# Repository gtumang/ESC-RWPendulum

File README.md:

# ESC-RWPendulum

Este repositório contém o firmware, modelos de simulação e ferramentas de visualização para um sistema de controle de **Pêndulo com Roda de Reação** (Pêndulo Invertido). O projeto foi projetado para estabilizar o pêndulo usando uma roda de reação acionada por um motor DC, controlado por um microcontrolador ESP32.

## Estrutura do Projeto

O repositório está organizado em quatro diretórios principais:

* **`Firmware/`**: Código C++ embarcado para o ESP32, construído usando PlatformIO. Gerencia a leitura de sensores, a execução da malha de controle e a comunicação serial.
* **`Matlab/`**: Scripts MATLAB e modelos Simulink para definição de parâmetros físicos, modelagem matemática e cálculo de ganho de controle (LQR).
* **`Visualization/`**: Scripts Python para telemetria em tempo real, registro de dados e plotagem via Serial.
* **`PCB/`**: Arquivos de projeto da placa de circuito impresso (Hardware), incluindo esquemáticos, layout e arquivos de fabricação.

---

## 1. Firmware (ESP32)

O firmware está localizado no diretório `Firmware` e está configurado como um projeto **PlatformIO**.

### Configuração de Hardware
* **Microcontrolador**: ESP32 (Placa: `fm-devkit`)
* **Atuador**: Motor DC com driver PWM (controlado pelos pinos 25/26).
* **Sensores**: Dois Encoders de Quadratura (Ângulo do Pêndulo e Velocidade da Roda).

**Pinagem (`main.cpp`):**
| Componente | Pino A | Pino B | Notas |
| :--- | :--- | :--- | :--- |
| **Encoder da Roda** | GPIO 17 | GPIO 16 | Mede velocidade/posição da roda de reação |
| **Encoder do Pêndulo** | GPIO 19 | GPIO 18 | Mede o ângulo de inclinação do pêndulo |
| **Driver do Motor** | GPIO 25 | GPIO 26 | Saída PWM (LEDC) |
| **Botão Iniciar/Parar**| GPIO 4 | - | Alterna a malha de controle (ISR) |

### Malha de Controle
* **Algoritmo**: Controle em Espaço de Estados (LQR).
* **Frequência**: 50 Hz (`Ts = 0.02s`).
* **Estados**:
    1.  $x_1$: Ângulo do Pêndulo (rad)
    2.  $x_2$: Ângulo da Roda (rad)
    3.  $x_3$: Velocidade do Pêndulo (rad/s)
    4.  $x_4$: Velocidade da Roda (rad/s)
* **Comunicação**: Envia dados de estado e esforço de controle via Serial (Formato binário).

---
## 2. MATLAB & Simulação

O diretório `Matlab` contém a fundação matemática do projeto.

* **`Scripts/SalvaParams.m`**: Define as constantes físicas do sistema (massas, comprimentos, inércia, constantes do motor) e as salva em `Parametros/parametros_planta.mat`.
    * *Parâmetros incluem:* $M_h$ (Massa da haste), $M_r$ (Massa do rotor), $L$ (Comprimento), $J_h$ (Inércia), etc.
* **`PenduloRotativoSim.slx`**: Modelo Simulink para simular a dinâmica do sistema e a resposta do controlador.
* **`Funcoes/`**: Contém funções geradas automaticamente (`function_G_Rot`, `function_M_Rot`, etc.) para a simulação não linear do sistema.
* **`Parametros/`**: Armazena arquivos `.mat` com a matriz de ganho de controle `K` calculada.

**Como usar:**
1.  Edite os parâmetros físicos em `SalvaParams.m` e execute-o.
2.  Execute o script de análise principal (ex: `main.mlx`) para calcular a matriz de ganho LQR $K$.
3.  Atualize a struct `K` em `Firmware/src/main.cpp` com os valores calculados.

---

## 3. Visualização (Python)

O diretório `Visualization` fornece ferramentas para visualizar dados do sistema em tempo real.

### Requisitos
* Python 3.x
* Bibliotecas: `pyserial`, `matplotlib`

### Scripts
* **`ler_pendulo.py`**: Um utilitário simples para ler dados brutos da porta serial e imprimir os valores decodificados em ponto flutuante no console.
* **`plot_pendulo.py`**: Uma ferramenta de plotagem em tempo real.
    * **Uso**: `python plot_pendulo.py --port COM3`
    * **Recursos**:
        * Plota múltiplas variáveis dinamicamente.
        * Suporta um modo de simulação para testar a interface sem hardware: `python plot_pendulo.py --sim`.
        * Visualiza Ângulo, Velocidade e Esforço de Controle ($u$).

---

## 4. Hardware e PCB (KiCad)

O diretório **`PCB`** contém todo o projeto eletrônico necessário para fabricar a placa de controle customizada do pêndulo, desenvolvido no software **KiCad**.

### Estrutura dos Arquivos
* **`RWPendulum/`**: Contém os arquivos fonte do projeto KiCad, incluindo o esquemático (`.kicad_sch`) e o layout da PCB (`.kicad_pcb`). O design integra o módulo ESP32 DevKit V1 e o driver de motor.
* **`OutputFiles/`**: Arquivos gerados para fabricação da placa:
    * **`Gerber/`**: Arquivos Gerber para as camadas de cobre, máscara de solda e corte.
    * **`Drill/`**: Arquivos de furação (PTH e NPTH).
* **`3D/`**: Modelos 3D (.step) da placa completa e componentes específicos (ex: Driver MD36A) para visualização mecânica e validação de encaixe.

---

## Licença
*Nenhuma licença especificada nos arquivos do repositório*.

## Autor
**Gabriel Brunoro Motta Tumang**

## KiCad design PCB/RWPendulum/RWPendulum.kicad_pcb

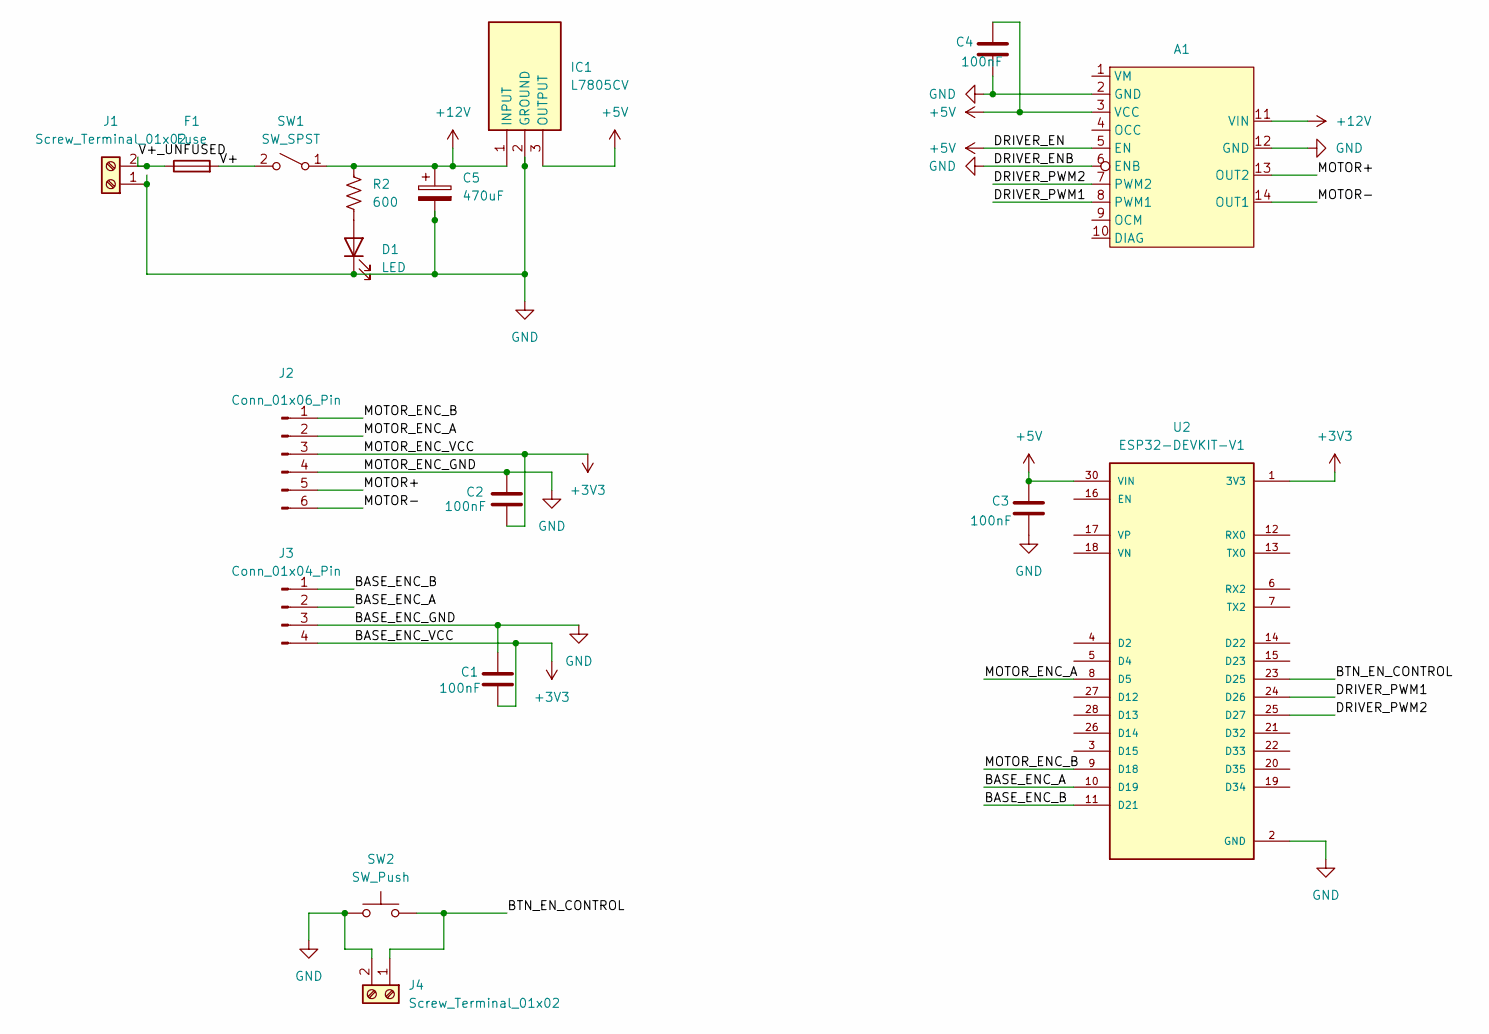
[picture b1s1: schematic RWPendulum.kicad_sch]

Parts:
A1: MD36A Motor Driver Header
C1, C2, C3, C4: 100nF; C_Disc_D5.0mm_W2.5mm_P5.00mm
C5: 470uF; CP_Radial_D8.0mm_P3.50mm
D1: LED; LED_D3.0mm
F1: Fuse; Fuseholder_Cylinder-5x20mm_Schurter_0031_8201_Horizontal_Op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
IC1: L7805CV; TO255P460X1020X2008-3P; Manufacturer_Part_Number L7805CV; Mouser Part Number 511-L7805CV
J1, J4: Screw_Terminal_01x02; TerminalBlock_MaiXu_MX126-5.0-02P_1x02_P5.00mm
J2: Conn_01x06_Pin; Molex_KK-396_A-41792-0006_1x06_P3.96mm_Horizontal
J3: Conn_01x04_Pin; Molex_KK-396_A-41792-0004_1x04_P3.96mm_Horizontal
R2: 600; R_Axial_DIN0207_L6.3mm_D2.5mm_P10.16mm_Horizontal
SW1: SW_SPST; TerminalBlock_MaiXu_MX126-5.0-02P_1x02_P5.00mm
SW2: SW_Push; SW_PUSH_6mm_H4.3mm
U2: ESP32-DEVKIT-V1; ESP32-C3-DevKitM-1; PARTREV N/A

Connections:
+3V3: C1.2, C2.2, J2.3, J3.4, U2.1 (3V3)
+5V: A1.3 (VCC), A1.5 (EN), C3.1, C4.1, IC1.3 (OUTPUT), U2.30 (VIN)
+12V: A1.11 (VIN), C5.1, IC1.1 (INPUT), R2.2, SW1.1 (A)
/BASE_ENC_A: J3.2, U2.10 (D19)
/BASE_ENC_B: J3.1, U2.11 (D21)
/BTN_EN_CONTROL: J4.1, SW2.2, U2.23 (D25)
/DRIVER_PWM1: A1.8 (PWM1), U2.24 (D26)
/DRIVER_PWM2: A1.7 (PWM2), U2.25 (D27)
/MOTOR+: A1.13 (OUT2), J2.5
/MOTOR-: A1.14 (OUT1), J2.6
/MOTOR_ENC_A: J2.2, U2.8 (D5)
/MOTOR_ENC_B: J2.1, U2.9 (D18)
/V+: F1.2, SW1.2 (B)
/V+_UNFUSED: F1.1, J1.2
GND: A1.2 (GND), A1.6 (ENB), A1.12 (GND), C1.1, C2.1, C3.2, C4.2, C5.2, D1.1 (K), IC1.2 (GROUND), J1.1, J2.4, J3.3, J4.2, SW2.1, U2.2 (GND), U2.29 (GND)
unnamed: D1.2 (A), R2.1

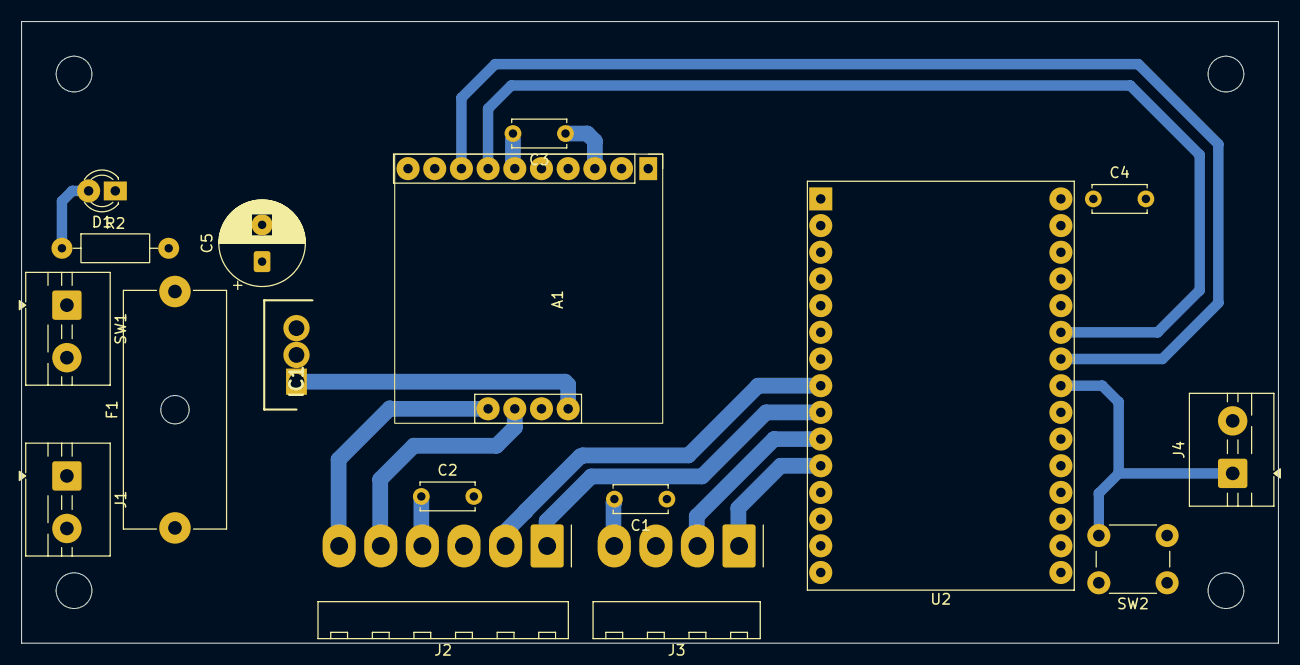
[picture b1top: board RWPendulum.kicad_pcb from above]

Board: 2 copper layers, 119.6 x 59.2 mm, 17 parts (0 on the bottom side), 16 nets.

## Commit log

2025-12-04 Commit inicial
    Adicionando arquivos de matlab contendo:
    - Modelagem do pendulo e sintonizacao do LQR
    - Simulink contendo simulação do pendulo
    - Arquivos de parâmetros
    - Funções de apoio para extração de parâmetros a partir de dados reais e geração do arquivo de parâmetros da planta
    - Dados reais da planta
2025-12-04 Criando diretório para matlab
2025-12-04 Adicionado arquivos fonte para firmware e para visualização em tempo real para PC
2025-12-04 Adicionando README
2025-12-24 Adicionado projeto da PCB e outras refatorações de diretórios e nomes de arquivos
2025-12-24 Atualziando readme para falar sobre o hardware
2025-12-24 Adicionando licença MIT
2025-12-24 Corrigindo nome do script SalvaParams.m
2025-12-24 Atualizando readme
2026-01-20 Atualizado design da PCB e arquivos gerber + drill
2026-01-26 Atualizando pinos de GPIO para utilizar a planta com PCB
2026-01-26 PCB: Rev. 1 - Gabriel Tumang - 22/01/2026
    Mudando pino do botão EN_CONTROL para 27 no lugar do 34 para utilizar função de pullup interno da ESP32,
    por consequência, os pinos de PWM p/ o driver foram modvidos para facilitar o roteamento.
    Também foram alterados tamanhos dos furos e pads de alguns componentes para tentar minimizar problemas de fabricação.
2026-03-09 Implementação do ESC e adicionado script para enviar dados de simulação para visualização
2026-03-09 - Criando projeto UV para visualização serial. - Separando definições para arquivo defines.h
